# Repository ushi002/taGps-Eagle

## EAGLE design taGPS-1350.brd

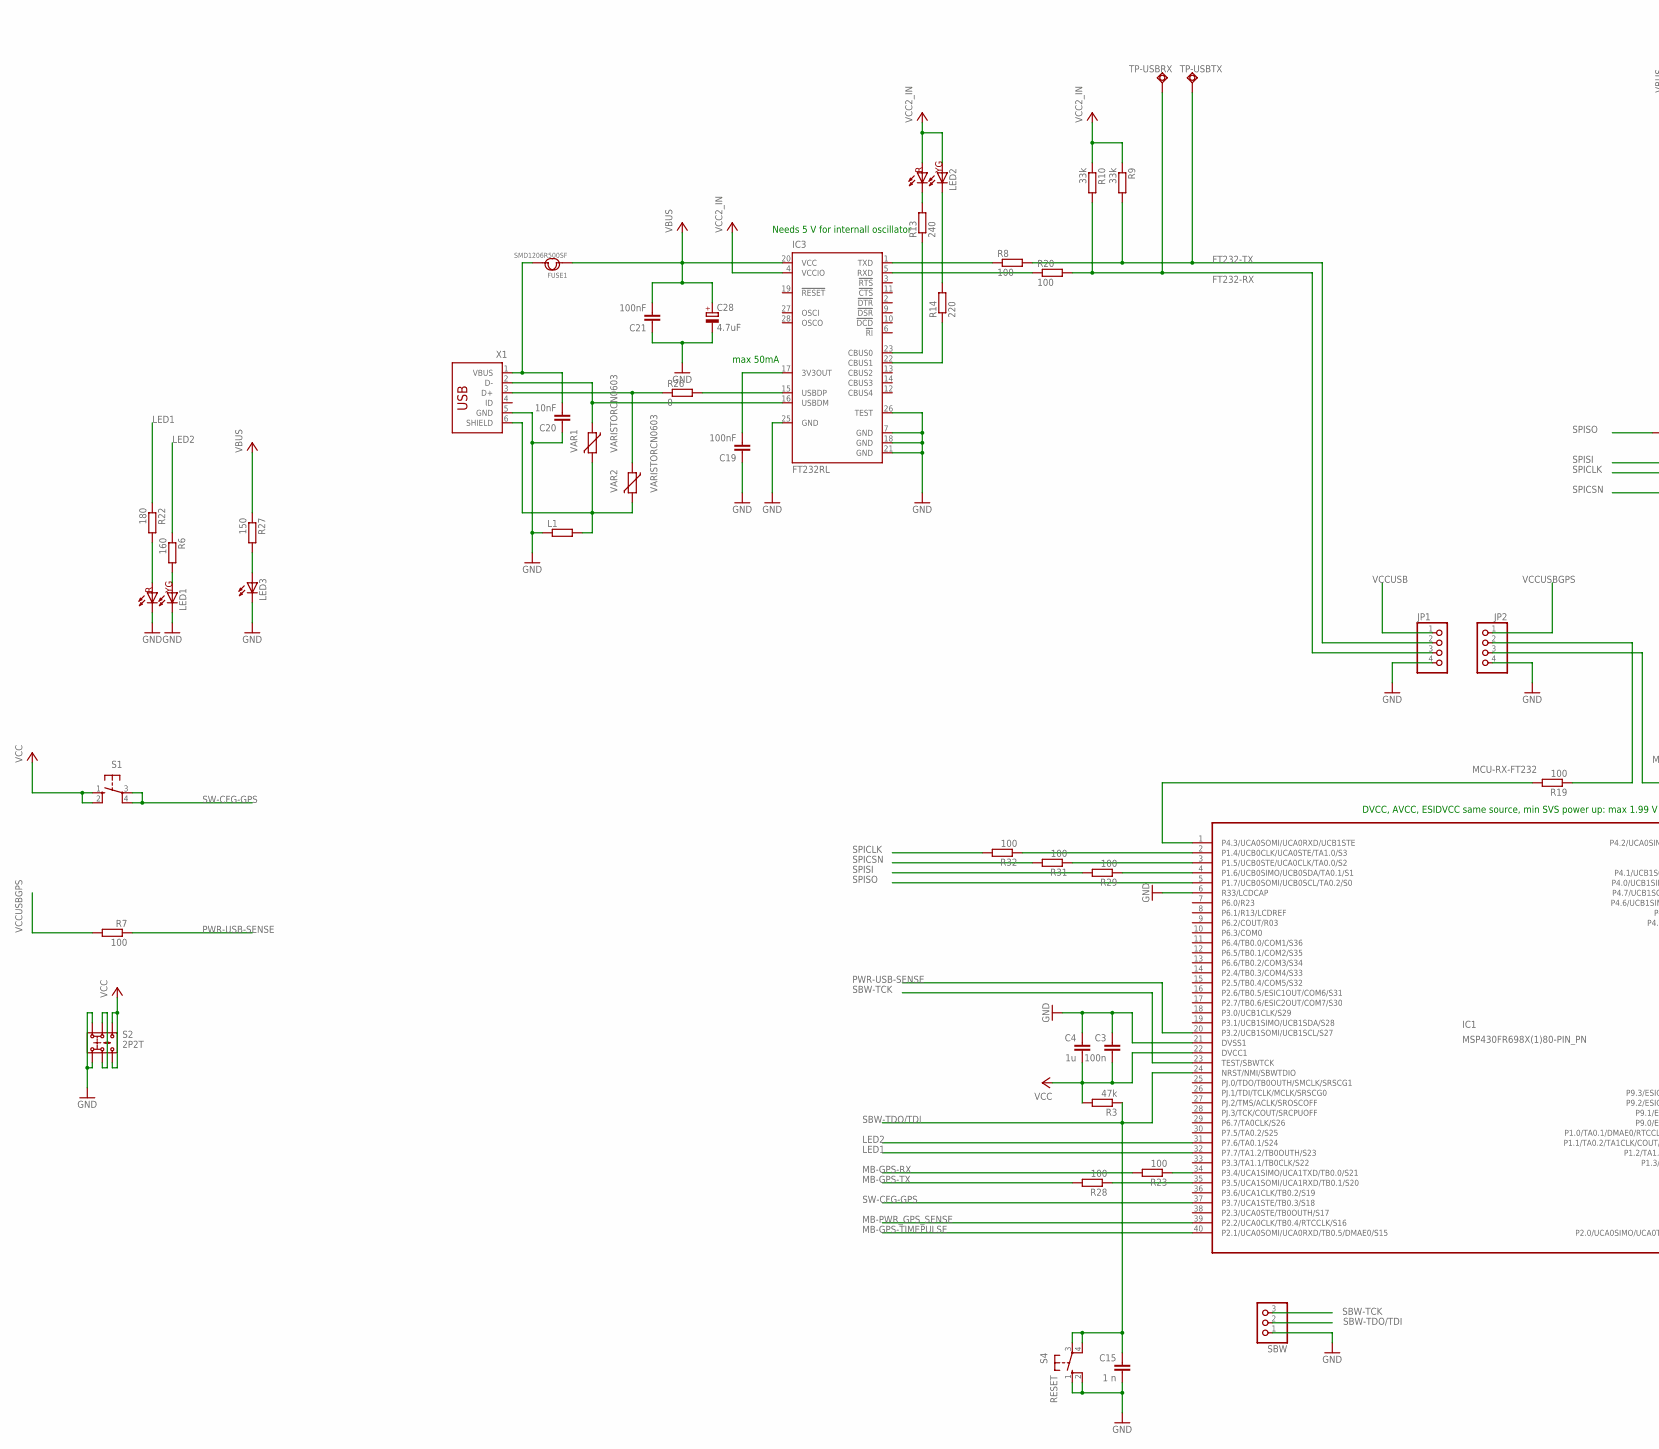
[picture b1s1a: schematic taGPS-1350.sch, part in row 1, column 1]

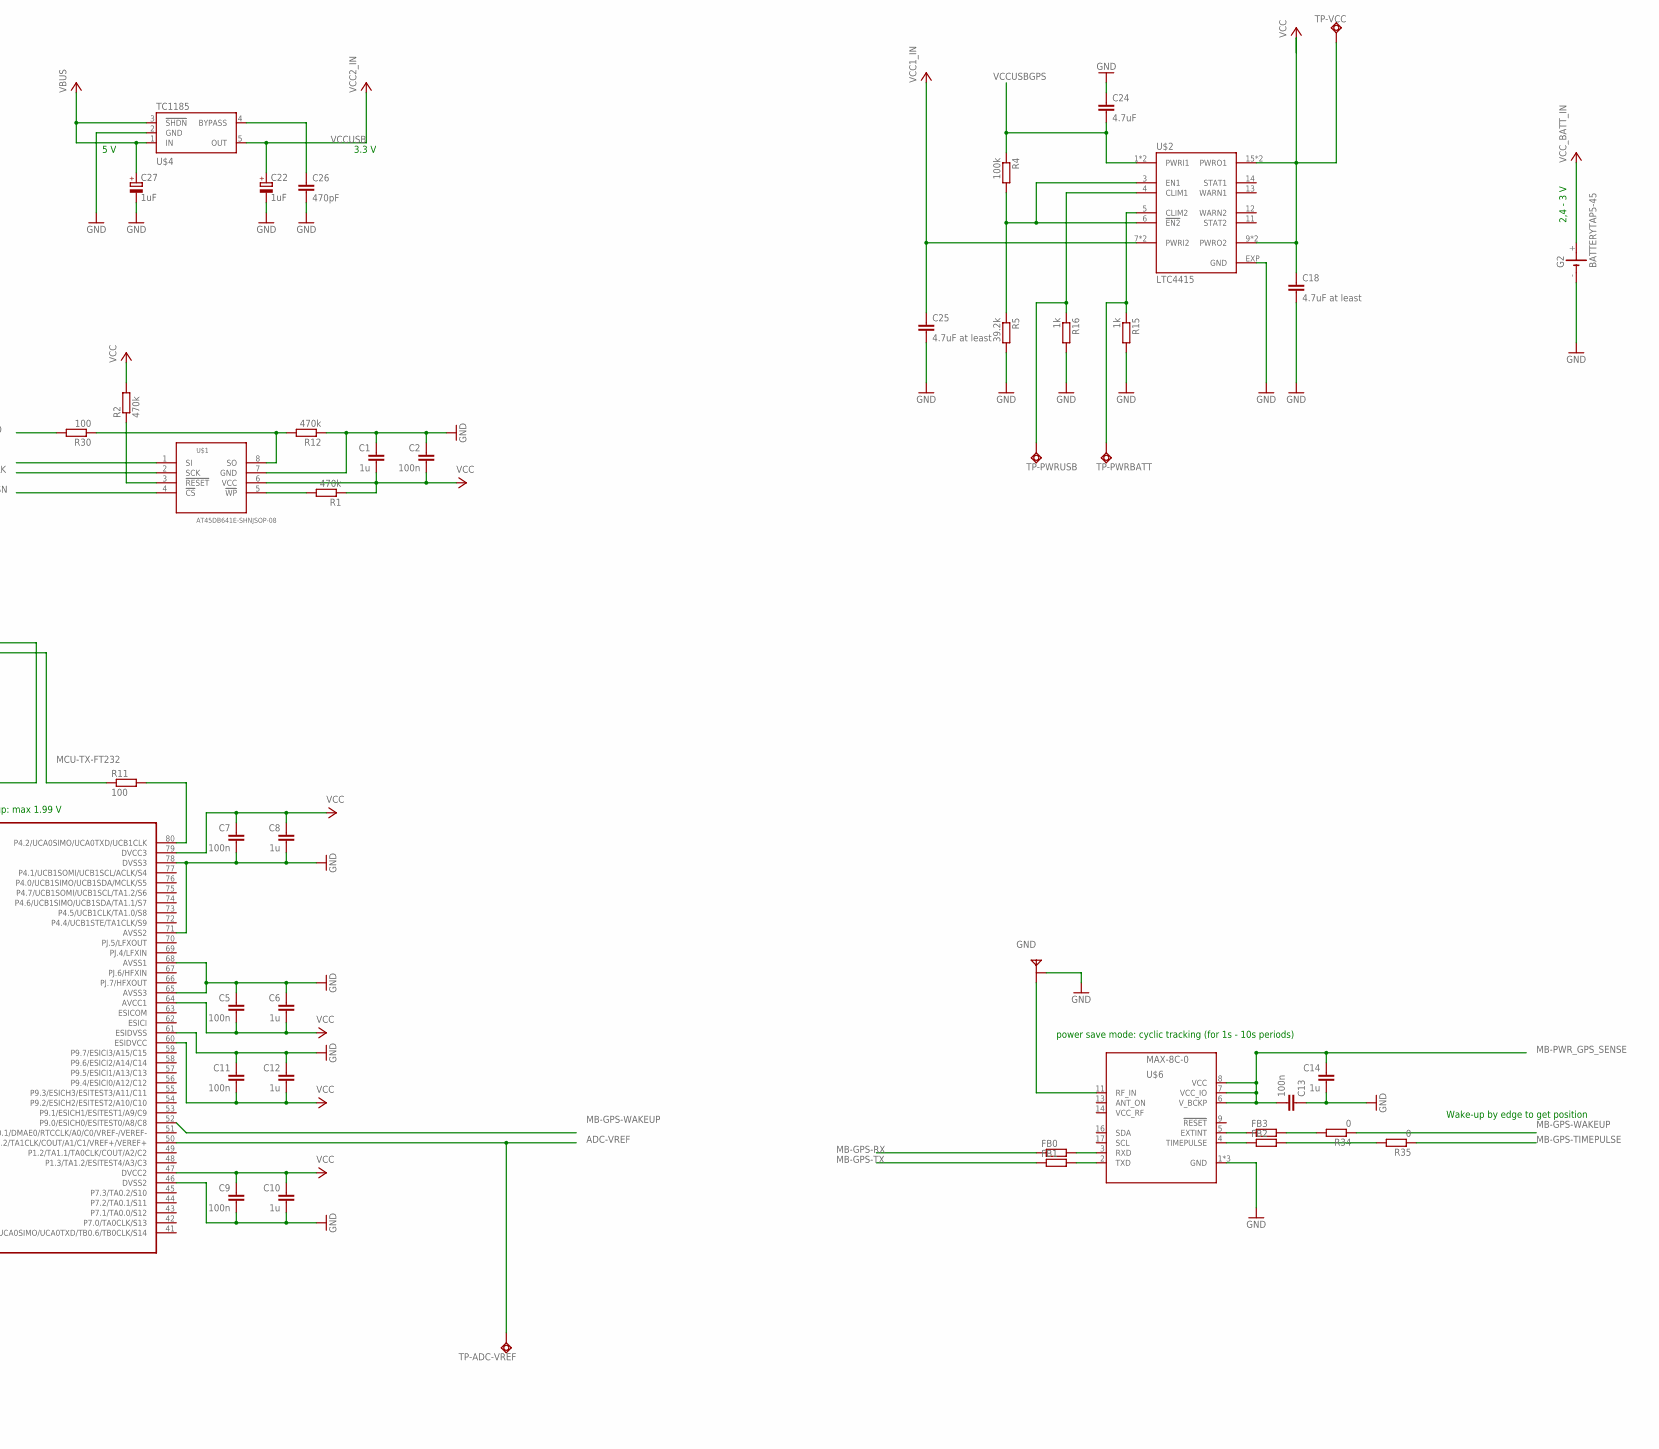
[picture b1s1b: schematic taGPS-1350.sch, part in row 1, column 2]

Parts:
C1, C4, C6, C8, C10, C12, C14: 1u; C0603
C2, C3, C5, C7, C9, C11, C13: 100n; C0603
C15: 1 n; C0603
C18, C25: 4.7uF at least; C0805
C19, C21: 100nF; C0603
C20: 10nF; C0603
C22, C27: 1uF; A/3216-18W
C24: 4.7uF; C0805
C26: 470pF; C0603
C28: 4.7uF; A/3216-18W
FB0, FB1, FB2, FB3: R-EU_R0402; R0402
FUSE1: SMD1206R500SF; F1812
G2: BATTERYTAP5-45; TAP5-45
IC1: MSP430FR698X(1)80-PIN_PN; PN_S-PQFP-G80
IC3: FT232RL; SSOP28
JP1, JP2: PINHD-1X4; 1X04
L1: R-EU_R0603; R0603
LED1, LED2: BILEDBILED; BILED
LED3: LED_E; LED_KINGBRIGHT0603
R1, R2, R12: 470k; R0603
R3: 47k; R0603
R4: 100k; R0603
R5: 39.2k; R0603
R6: 160; R0603
R7, R8, R11, R19, R20, R23, R28, R29, R30, R31, R32: 100; R0603
R9, R10: 33k; R0603
R13: 240; R0603
R14: 220; R0603
R15, R16: 1k; R0603
R22: 180; R0603
R26, R34, R35: 0; R0603
R27: 150; R0603
S1: SWITCH-10-XX; B3F-10XX
S2: 2P2T
S4: RESET; B3F-10XX
SBW: PINHD-1X3; 1X03
TP-ADC-VREF: TPSQTP10R; TP10R
TP-PWRBATT: TPSQTP10R; TP10R
TP-PWRUSB: TPSQTP10R; TP10R
TP-USBRX: TPSQPAD1-13; P1-13
TP-USBTX: TPSQPAD1-13; P1-13
TP-VCC: TPSQTP10R; TP10R
U$1: AT45DB641E-SHNJSOP-08; JSOP-08
U$2: LTC4415; MSOP16
U$4: TC1185; SOT23-5
U$5: MWSL1251MWSL1350; MWSL1350
U$6: MAX-8C-0; MAX-8
VAR1, VAR2: VARISTORCN0603; CT/CN0603
X1: USB-787616; USB

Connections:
ADC-BATT: R15.1, TP-PWRBATT.TP, U$2.5 (CLIM2)
ADC-VREF: IC1.50 (P1.1/TA0.2/TA1CLK/COUT/A1/C1/VREF+/VERE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), TP-ADC-VREF.TP
FT232-RX: JP1.3, R10.2, R20.2, TP-USBRX.TP
FT232-TX: JP1.2, R8.2, R9.2, TP-USBTX.TP
GND: C1.1, C2.1, C3.1, C4.1, C5.1, C6.1, C7.2, C8.2, C9.2, C10.2, C11.1, C12.1, C13.1, C14.2, C15.2, C18.2, C19.1, C20.1, C21.1, C22.-, C24.1, C25.2, C26.2, C27.-, C28.-, G2.-, IC1.6 (R33/LCDCAP), IC1.21 (DVSS1), IC1.46 (DVSS2), IC1.61 (ESIDVSS), IC1.65 (AVSS3), IC1.68 (AVSS1), IC1.71 (AVSS2), IC1.78 (DVSS3), IC3.7 (GND), IC3.18 (GND), IC3.21 (GND), IC3.25 (GND), IC3.26 (TEST), JP1.4, JP2.4, L1.1, LED1.1, LED1.3, LED3.C, R5.2, R12.1, R15.2, R16.2, S2.1.1, S2.1.2, S4.1 (S), S4.2 (S1), SBW.1, U$1.7 (GND), U$2.EXP (GND), U$4.2 (GND), U$5.P$1 (GND), U$5.P$3 (GND), U$6.1 (GND), U$6.10 (GND), U$6.12 (GND), X1.5 (GND)
LED1: IC1.32 (P7.7/TA1.2/TB0OUTH/S23), R22.1
LED2: IC1.31 (P7.6/TA0.1/S24), R6.1
MB-GPS-RX: FB0.1, R23.2
MB-GPS-TIMEPULSE: IC1.40 (P2.1/UCA0SOMI/UCA0RXD/TB0.5/DMAE0/S15), R35.1
MB-GPS-TX: FB1.1, R28.2
MB-GPS-WAKEUP: IC1.52 (P9.0/ESICH0/ESITEST0/A8/C8), R34.1
MB-PWR_GPS_SENSE: C13.2, C14.1, IC1.39 (P2.2/UCA0CLK/TB0.4/RTCCLK/S16), S2.2.1, S2.2.2, U$6.6 (V_BCKP), U$6.7 (VCC_IO), U$6.8 (VCC)
MCU-RX-FT232: IC1.1 (P4.3/UCA0SOMI/UCA0RXD/UCB1STE), R19.2
MCU-TX-FT232: JP2.3, R11.1
unnamed: IC3.1 (TXD), R8.1
unnamed: IC1.80 (P4.2/UCA0SIMO/UCA0TXD/UCB1CLK), R11.2
unnamed: IC1.4 (P1.6/UCB0SIMO/UCB0SDA/TA0.1/S1), R29.1
unnamed: IC3.5 (RXD), R20.1
unnamed: R2.1, U$1.3 (!RESET)
unnamed: R4.2, R5.1, U$2.3 (EN1), U$2.6 (!EN2)
unnamed: JP2.2, R19.1
unnamed: C19.2, IC3.17 (3V3OUT)
unnamed: R1.2, U$1.5 (!WP)
unnamed: R26.1, VAR2.1, X1.3 (D+)
unnamed: IC3.16 (USBDM), VAR1.1, X1.2 (D-)
unnamed: R12.2, R30.1, U$1.8 (SO)
unnamed: FB0.2, U$6.3 (RXD)
unnamed: IC3.23 (CBUS0), R13.1
unnamed: IC3.22 (CBUS1), R14.1
unnamed: LED2.1, R13.2
unnamed: LED2.3, R14.2
unnamed: C20.2, FUSE1.2, X1.1 (VBUS)
unnamed: L1.2, VAR1.2, VAR2.2, X1.6 (SHIELD)
unnamed: IC1.2 (P1.4/UCB0CLK/UCA0STE/TA1.0/S3), R32.1
unnamed: R16.1, TP-PWRUSB.TP, U$2.4 (CLIM1)
unnamed: FB1.2, U$6.2 (TXD)
unnamed: U$5.P$2 (FEED), U$6.11 (RF_IN)
unnamed: IC3.15 (USBDP), R26.2
unnamed: C26.1, U$4.4 (BYPASS)
unnamed: LED1.4, R6.2
unnamed: LED1.2, R22.2
unnamed: IC1.3 (P1.5/UCB0STE/UCA0CLK/TA0.0/S2), R31.1
unnamed: IC1.34 (P3.4/UCA1SIMO/UCA1TXD/TB0.0/S21), R23.1
unnamed: LED3.A, R27.2
unnamed: IC1.35 (P3.5/UCA1SOMI/UCA1RXD/TB0.1/S20), R28.1
unnamed: FB3.2, R34.2
unnamed: FB2.2, R35.2
unnamed: FB2.1, U$6.4 (TIMEPULSE)
unnamed: FB3.1, U$6.5 (EXTINT)
PWR-USB-SENSE: IC1.20 (P3.2/UCB1SOMI/UCB1SCL/S27), R7.1
SBW-TCK: IC1.23 (TEST/SBWTCK), SBW.3
SBW-TDO/TDI: C15.1, IC1.24 (NRST/NMI/SBWTDIO), R3.1, S4.3, S4.4 (P1), SBW.2
SPICLK: R32.2, U$1.2 (SCK)
SPICSN: R31.2, U$1.4 (!CS)
SPISI: R29.2, U$1.1 (SI)
SPISO: IC1.5 (P1.7/UCB0SOMI/UCB0SCL/TA0.2/S0), R30.2
SW-CFG-GPS: IC1.37 (P3.7/UCA1STE/TB0.3/S18), S1.3, S1.4 (P1)
VBUS: C21.2, C27.+, C28.+, FUSE1.1, IC3.20 (VCC), R27.1, U$4.1 (IN), U$4.3 (!SHDN)
VCC: C1.2, C2.2, C3.2, C4.2, C5.2, C6.2, C7.1, C8.1, C9.1, C10.1, C11.2, C12.2, C18.1, IC1.22 (DVCC1), IC1.47 (DVCC2), IC1.60 (ESIDVCC), IC1.64 (AVCC1), IC1.79 (DVCC3), R1.1, R2.2, R3.2, S1.1 (S), S1.2 (S1), S2.3.1, S2.3.2, TP-VCC.TP, U$1.6 (VCC), U$2.9 (PWRO2), U$2.10 (PWRO2), U$2.15 (PWRO1), U$2.16 (PWRO1)
VCCUSB: C22.+, IC3.4 (VCCIO), JP1.1, LED2.2, LED2.4, R9.1, R10.1, U$4.5 (OUT)
VCCUSBGPS: C24.2, JP2.1, R4.1, R7.2, U$2.1 (PWRI1), U$2.2 (PWRI1)
VCC_BATT_IN: C25.1, G2.+, U$2.7 (PWRI2), U$2.8 (PWRI2)

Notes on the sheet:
2,4 - 3 V
DVCC, AVCC, ESIDVCC same source, min SVS power up: max 1.99 V
Needs 5 V for internall oscillator
5 V
3.3 V
max 50mA
power save mode: cyclic tracking (for 1s - 10s periods)
Wake-up by edge to get position

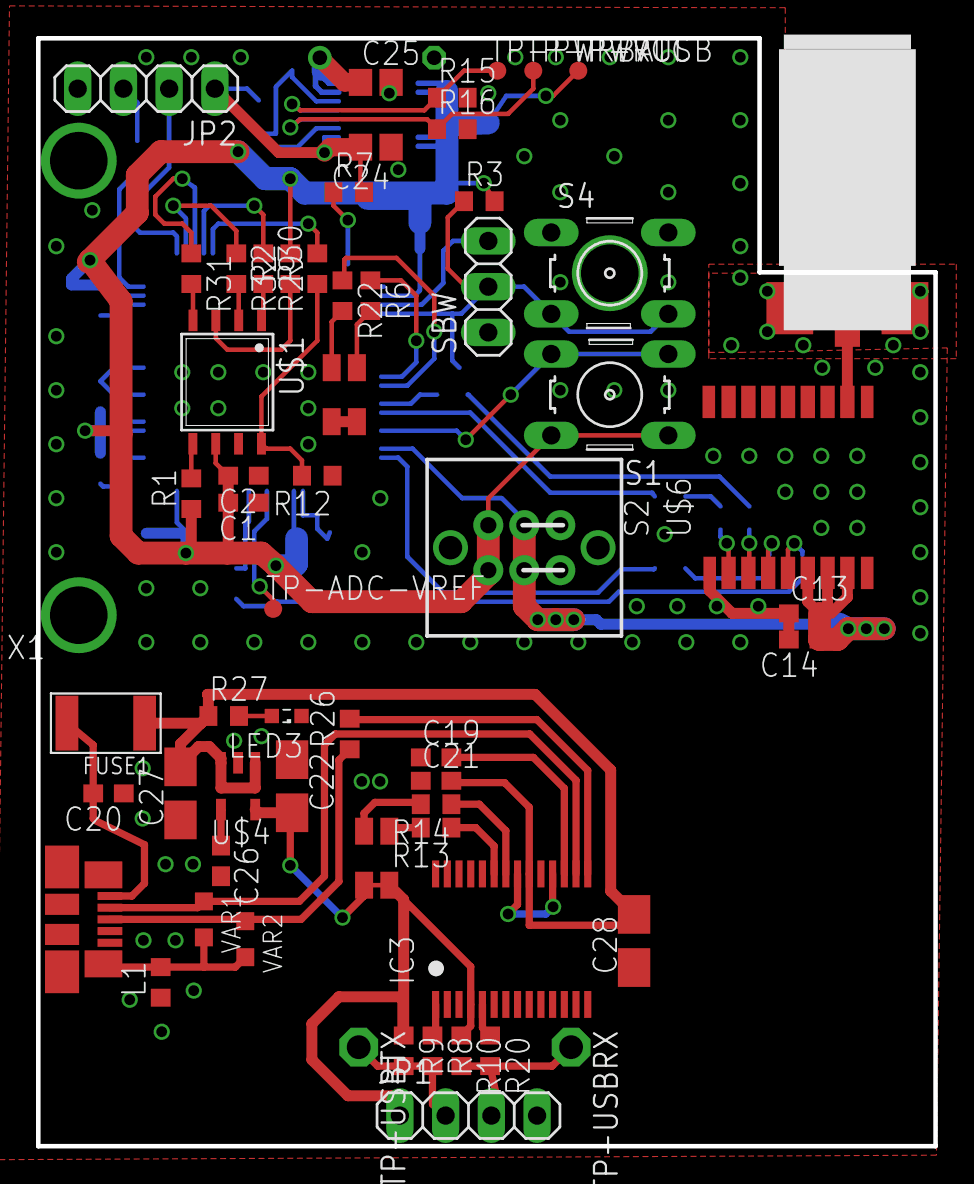
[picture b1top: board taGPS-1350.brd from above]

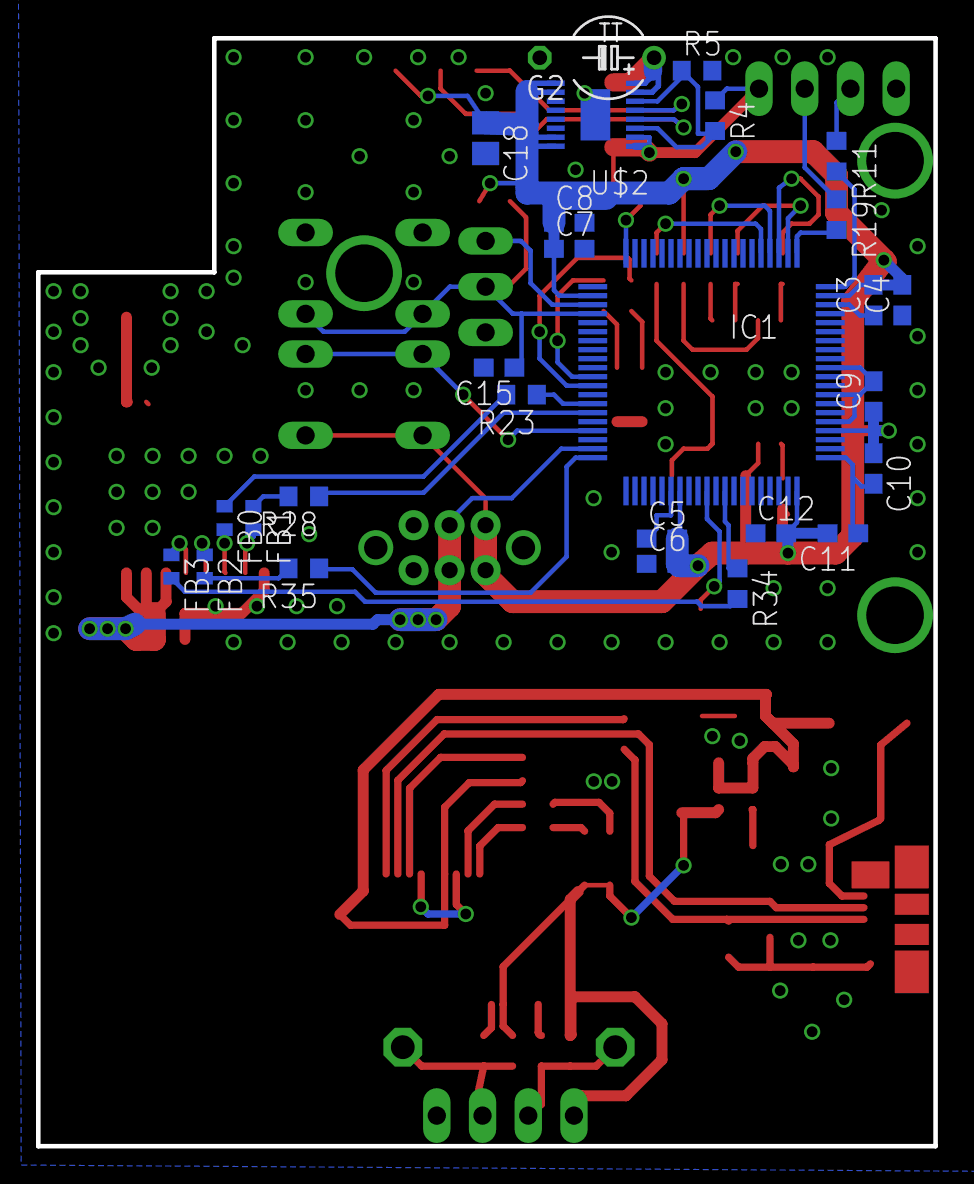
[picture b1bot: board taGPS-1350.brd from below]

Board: 2 copper layers, 49.9 x 61.5 mm, 86 parts (27 on the bottom side), 62 nets.

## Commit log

2015-01-27 Initial commit - TAGPS eagle scheme and board almost done
2015-01-28 Compress board space to minimum, place battery holder
2015-01-30 The board is almost done
2015-04-03 Added GPS chip, board mostly done, prepare for order
2015-04-09 Check DRC, fix overlaps, clearence
2015-04-14 Fix few clearances
2015-04-16 Improve few lbr (tagps) packages
2015-04-16 Improve board for pcb factory
2015-04-16 Fix clearance values, improve brd texts
2015-04-29 Change USB.pac text layer
2015-05-20 Fix msp430f5437 SMD PADs missing stop layer
2015-05-20 Turn on polygon thermals and fix one GND wire
2015-12-27 Move GPS-TIMEPULSE sig to interrupt capable input (P2.1)
2016-01-27 Redesign a lot GPS RF part, CPU pins
2016-01-28 Patch antenna module done
2016-01-28 Fix CANAL sliding switch
2016-01-29 Add MWSL1251 antenna to taGPS library
2016-01-29 Add MWSL1251 antenna to taGPS design
2016-01-29 Small board tuning
2016-01-30 Rotate connector of patch antenna
2016-01-31 Add ceramic antenna, move the patch antenna connetor a bit
2016-01-31 Fix gps-power switch scheme
2016-02-01 More PCB board tuning
2016-03-16 fix power-switcher voltage divider resistor value
2016-03-16 Add text TST-RST-GND to pcb program pins
2016-03-31 Fix SPI flash package foot print on PCB
2016-03-31 Resize Cc and Rs from 0805->0603
2016-04-05 Split board to 2 pieces, remove ADC battery input (was senseless)
2016-04-05 Remove UART pullups and button to make it even smaller
    Removed GPS and USB pullups (do not forget to add them
    to the MCU IOs!), removed one button, removed unnecesary
    GPS ferrite beads
2016-04-05 Add MWSL1350 package
2016-04-06 Add design with MWSL1350 antenna
2016-04-06 Add design with MWSL1251 antenna
2016-04-11 Fix MCU RX/TX pinheader position, polish boards
2016-04-12 Add restrict field for micro-usb package
2016-04-12 Add seeed FUSE 1812 to library
2016-04-12 Replace FUSE package to 1812
2016-04-12 Add panel-gps.brd (v1350 and v1251 for manufacturing)
2016-04-20 Check rules acc seeed studio
2016-04-20 Little panel tuning
2016-04-22 Redesign type 1350 to get wider copper plane for antenna
2016-04-22 Update panel-gps massively, add holes
2016-04-24 Tune panel-gps a bit more (move holes, add text)
2016-05-27 Fix panel-gps board connector signal labels
2016-05-29 Fix MWSL1350 antenna device package sizes
2016-05-29 Fix antenna position, grounding
2016-05-30 Remove DC power shunts
2016-06-01 Add Ferrite Beads for GPS chip, modify battery input
    For battery input one capacitor package was modified...
2016-06-01 Add gps-1350-v0.31 board for manufacturer
2016-06-03 Finish gps-1350-manu.brd and send it to china
2016-06-03 Backport 1350-manu.brd to 1350 design
2016-06-11 Fix 1350.brd timepulse resistor position
2016-06-11 Improve 1350.brd gps chip inductors position
